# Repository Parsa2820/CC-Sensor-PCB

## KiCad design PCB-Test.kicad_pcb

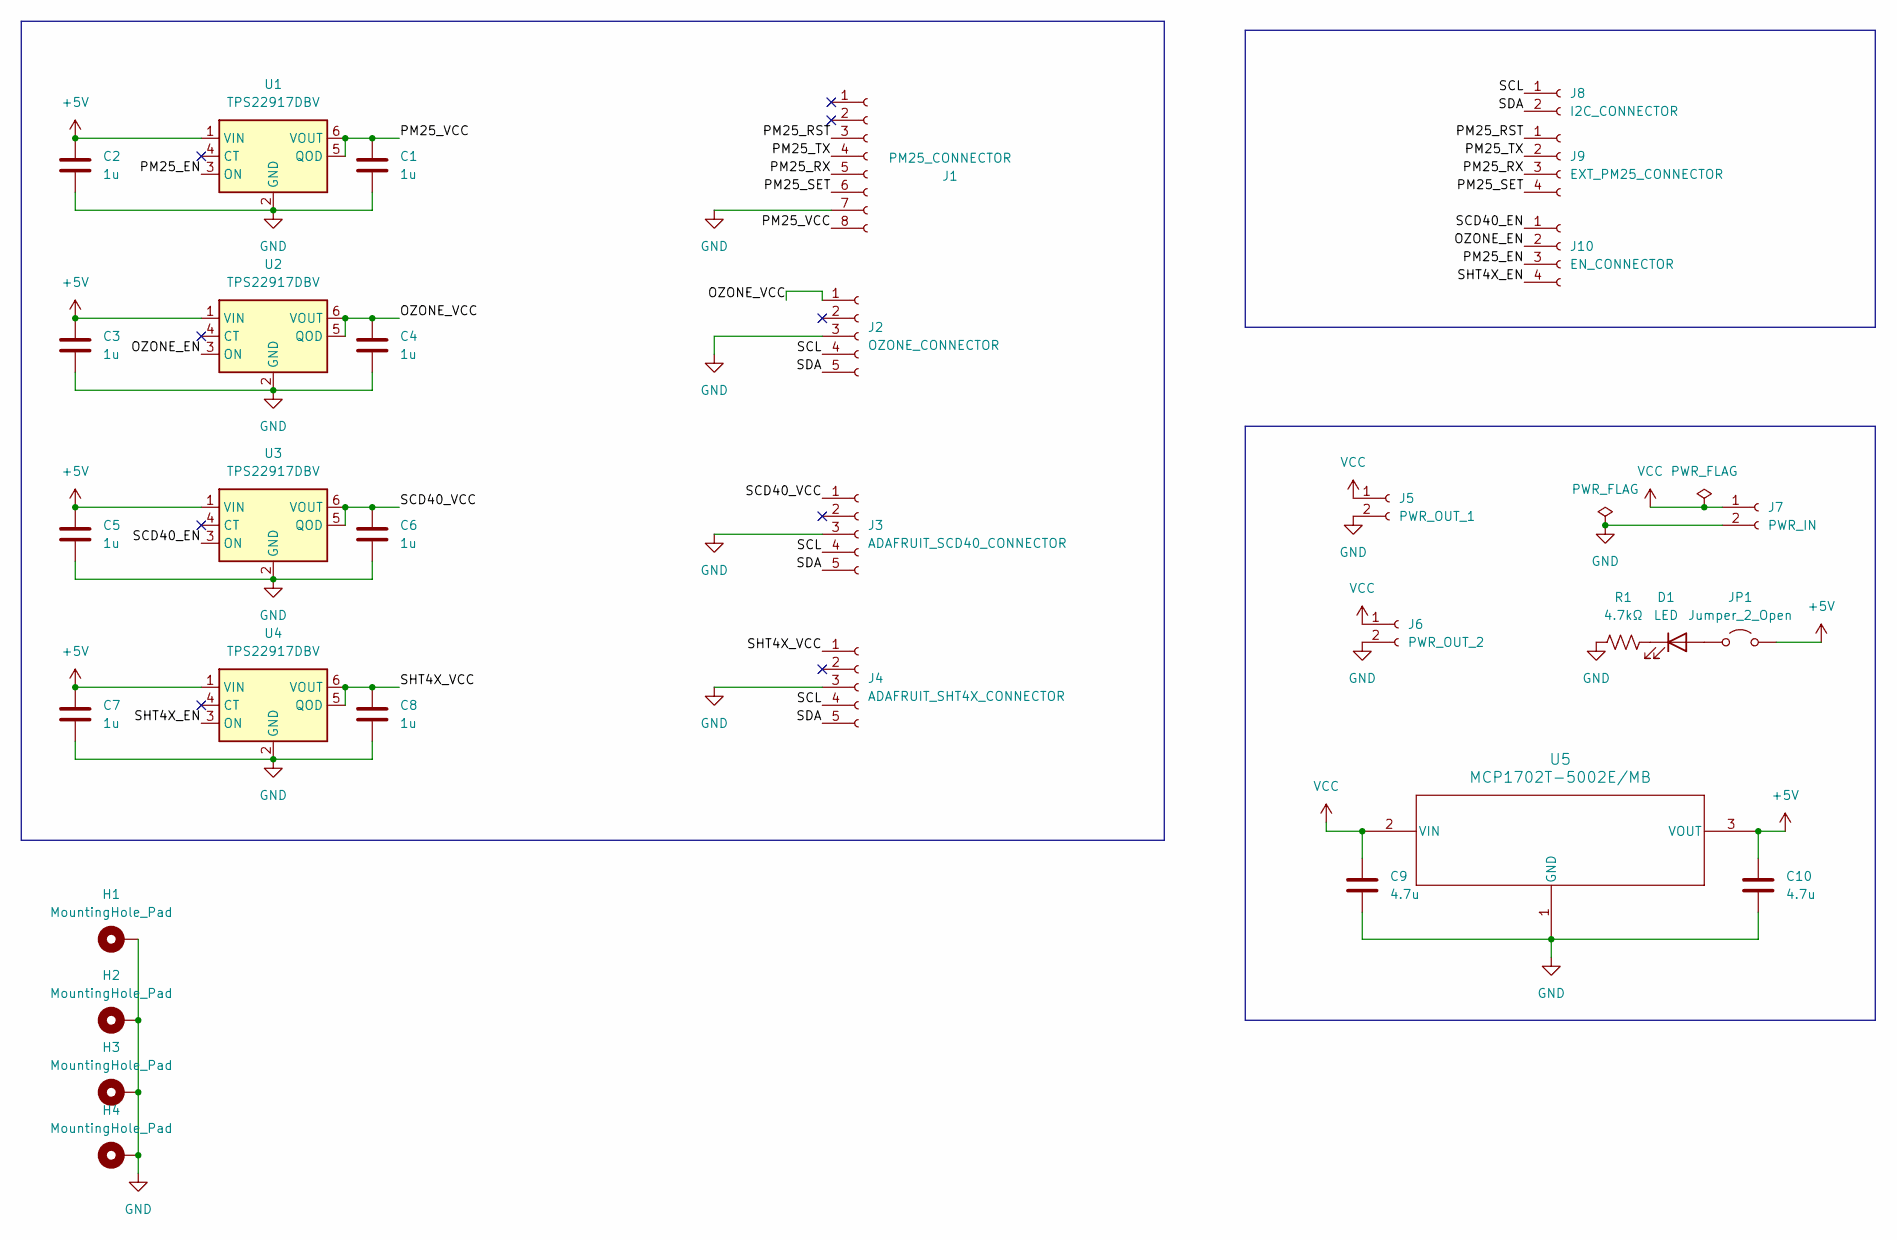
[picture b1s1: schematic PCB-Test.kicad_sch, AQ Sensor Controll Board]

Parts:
C1, C2, C3, C4, C5, C6, C7, C8: 1u; C_0805_2012Metric; LCSC C28323
C9, C10: 4.7u; C_0805_2012Metric; LCSC C1779
D1: LED; LED_0603_1608Metric; LCSC C2286
H1, H2, H3, H4: MountingHole_Pad; MountingHole_3.2mm_M3_Pad_Via
J1: PM25_CONNECTOR; Molex_PicoBlade_53047-0810_1x08_P1.25mm_Vertical; LCSC C240845
J2: OZONE_CONNECTOR; PinHeader_1x05_P2.54mm_Vertical
J3: ADAFRUIT_SCD40_CONNECTOR; PinSocket_1x05_P2.54mm_Vertical
J4: ADAFRUIT_SHT4X_CONNECTOR; PinSocket_1x05_P2.54mm_Vertical
J5: PWR_OUT_1; PinHeader_1x02_P2.54mm_Vertical
J6: PWR_OUT_2; PinHeader_1x02_P2.54mm_Vertical
J7: PWR_IN; PinHeader_1x02_P2.54mm_Vertical
J8: I2C_CONNECTOR; PinHeader_1x02_P2.54mm_Vertical
J9: EXT_PM25_CONNECTOR; PinHeader_1x04_P2.54mm_Vertical
J10: EN_CONNECTOR; PinHeader_1x04_P2.54mm_Vertical
JP1: Jumper_2_Open; PinHeader_1x02_P2.54mm_Vertical
R1: 4.7kΩ; R_0603_1608Metric; LCSC C23162
U1, U2, U3, U4: TPS22917DBV; SOT-23-6; LCSC C2681320
U5: MCP1702T-5002E/MB; SOT-89-3; LCSC C18299

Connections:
+5V: C2.1, C3.1, C5.1, C7.1, C10.1, JP1.2 (B), U1.1 (VIN), U2.1 (VIN), U3.1 (VIN), U4.1 (VIN), U5.3 (VOUT)
/OZONE_EN: J10.2, U2.3 (ON)
/OZONE_VCC: C4.1, J2.1, U2.5 (QOD), U2.6 (VOUT)
/PM25_EN: J10.3, U1.3 (ON)
/PM25_RST: J1.3, J9.1
/PM25_RX: J1.5, J9.3
/PM25_SET: J1.6, J9.4
/PM25_TX: J1.4, J9.2
/PM25_VCC: C1.1, J1.8, U1.5 (QOD), U1.6 (VOUT)
/SCD40_EN: J10.1, U3.3 (ON)
/SCD40_VCC: C6.1, J3.1, U3.5 (QOD), U3.6 (VOUT)
/SCL: J2.4, J3.4, J4.4, J8.1
/SDA: J2.5, J3.5, J4.5, J8.2
/SHT4X_EN: J10.4, U4.3 (ON)
/SHT4X_VCC: C8.1, J4.1, U4.5 (QOD), U4.6 (VOUT)
GND: C1.2, C2.2, C3.2, C4.2, C5.2, C6.2, C7.2, C8.2, C9.2, C10.2, H1.1, H2.1, H3.1, H4.1, J1.7, J2.3, J3.3, J4.3, J5.2, J6.2, J7.2, R1.1, U1.2 (GND), U2.2 (GND), U3.2 (GND), U4.2 (GND), U5.1 (GND)
unnamed: D1.2 (A), JP1.1 (A)
unnamed: D1.1 (K), R1.2
VCC: C9.1, J5.1, J6.1, J7.1, U5.2 (VIN)

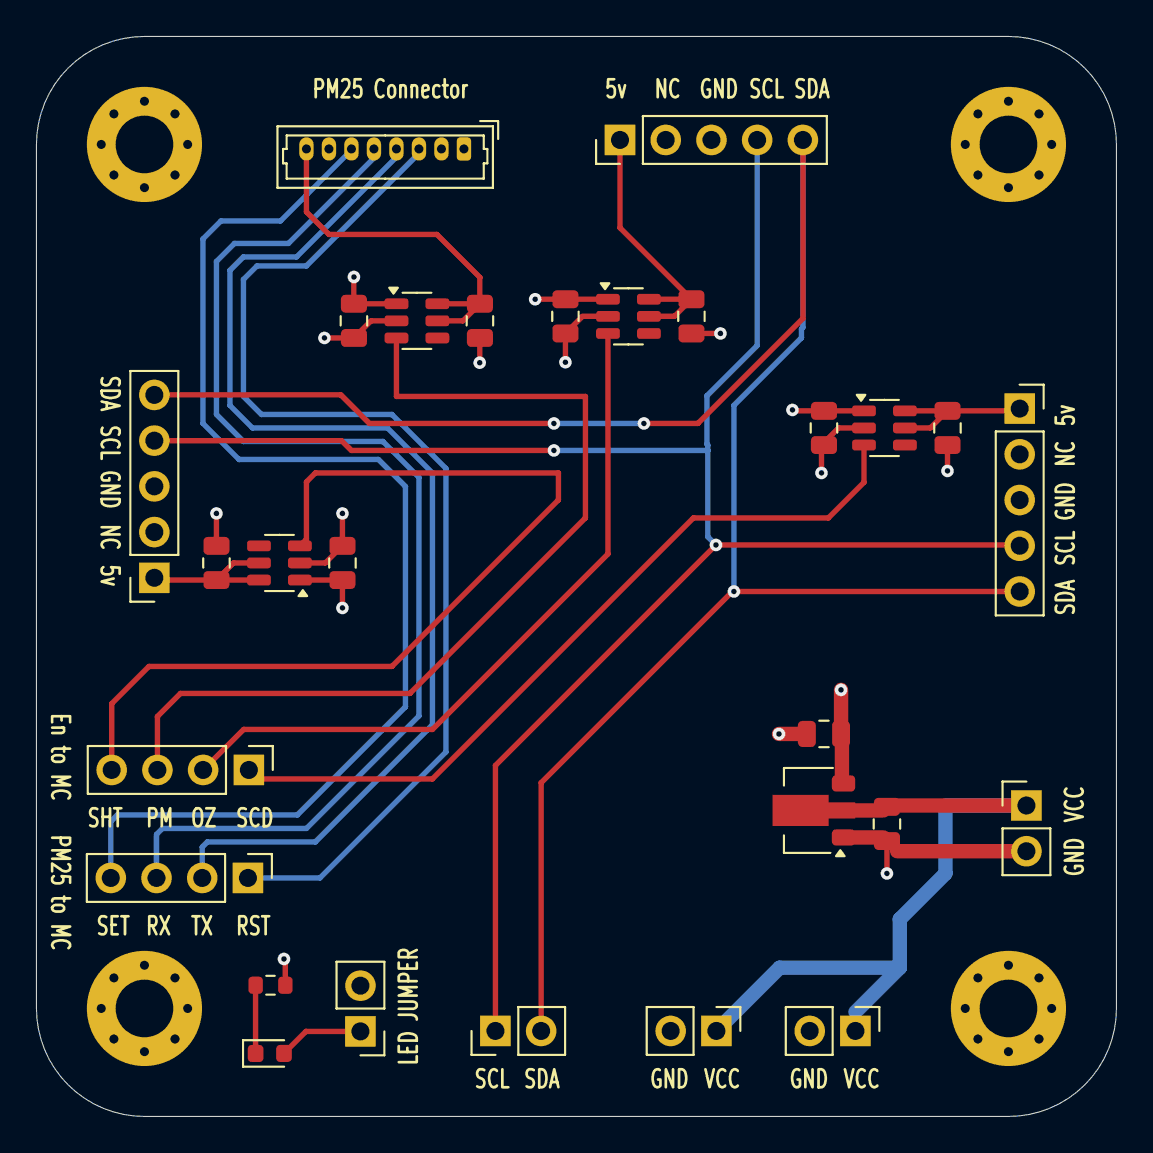
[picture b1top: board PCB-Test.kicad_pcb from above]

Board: 4 copper layers, 60.0 x 60.0 mm, 32 parts (0 on the bottom side), 19 nets.

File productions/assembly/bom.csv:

"Reference","Value","Footprint","Qty","DNP","LCSC"
"C1,C2,C3,C4,C5,C6,C7,C8","1u","Capacitor_SMD:C_0805_2012Metric","8","","C28323"
"C9,C10","4.7u","Capacitor_SMD:C_0805_2012Metric","2","","C1779"
"D1","LED","LED_SMD:LED_0603_1608Metric","1","","C2286"
"J1","PM25_CONNECTOR","Connector_Molex:Molex_PicoBlade_53047-0810_1x08_P1.25mm_Vertical","1","","C240845"
"J2","OZONE_CONNECTOR","Connector_PinHeader_2.54mm:PinHeader_1x05_P2.54mm_Vertical","1","",""
"J3","ADAFRUIT_SCD40_CONNECTOR","Connector_PinSocket_2.54mm:PinSocket_1x05_P2.54mm_Vertical","1","",""
"J4","ADAFRUIT_SHT4X_CONNECTOR","Connector_PinSocket_2.54mm:PinSocket_1x05_P2.54mm_Vertical","1","",""
"J5","PWR_OUT_1","Connector_PinHeader_2.54mm:PinHeader_1x02_P2.54mm_Vertical","1","",""
"J6","PWR_OUT_2","Connector_PinHeader_2.54mm:PinHeader_1x02_P2.54mm_Vertical","1","",""
"J7","PWR_IN","Connector_PinHeader_2.54mm:PinHeader_1x02_P2.54mm_Vertical","1","",""
"J8","I2C_CONNECTOR","Connector_PinHeader_2.54mm:PinHeader_1x02_P2.54mm_Vertical","1","",""
"J9","EXT_PM25_CONNECTOR","Connector_PinHeader_2.54mm:PinHeader_1x04_P2.54mm_Vertical","1","",""
"J10","EN_CONNECTOR","Connector_PinHeader_2.54mm:PinHeader_1x04_P2.54mm_Vertical","1","",""
"JP1","Jumper_2_Open","Connector_PinHeader_2.54mm:PinHeader_1x02_P2.54mm_Vertical","1","",""
"R1","4.7kΩ","Resistor_SMD:R_0603_1608Metric","1","","C23162"
"U1,U2,U3,U4","TPS22917DBV","Package_TO_SOT_SMD:SOT-23-6","4","","C2681320"
"U5","MCP1702T-5002E/MB","Package_TO_SOT_SMD:SOT-89-3","1","","C18299"

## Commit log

2025-02-21 Almost done
2025-03-13 Add BOM
2025-03-13 Generate production files
2025-03-21 Finalize
2025-06-27 Add bom files

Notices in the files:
PCB-Test.kicad_pcb:
COPYRIGHT 2025
